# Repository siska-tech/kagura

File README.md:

# 

Kinetic Audio & Graphics Unified Rendering Architecture。
Tang Nano 9K（GW1NR-9）1枚で動く、外部ホスト制御のHDMIビデオ・サウンドチップです。ホストは32 byteのレジスタ窓だけを操作し、FPGAが背景・spriteの描画、音源の合成、HDMI（映像＋48kHz音声）出力を行います。

*720pデモのRTLシミュレーション出力（論理320×180を1280×720へ4倍表示）。実機モニターの撮影ではありません。[画像の生成元](docs/images/README.md)。*

デモ動画（YouTube）: [KAGURA-9: Custom HDMI Video & 6-Channel Sound Chip](https://www.youtube.com/shorts/ZjfHmth6I0A)

*実機構成: Raspberry Pi Pico（SPI/QSPIホスト）とTang Nano 9K。配線は[Pico firmware](https://github.com/siska-tech/kagura-sdk/blob/aae8699d8db01ed9825b37443b8ff8f3bb1cd14b/software/pico/README.md)を参照。*

## Picoキャリアボード

<table>
<tr>
<td></td>
<td></td>
</tr>
<tr><td>表面：Tang Nano 9K・XIAO RP2040</td><td>裏面：Raspberry Pi Pico</td></tr>
</table>

Raspberry Pi Pico・Tang Nano 9K・XIAO RP2040をまとめる、72×48mm・4層の試作キャリアボードです。USB-Cからの5V給電、USB-Aホスト端子、3.3V Grove I2C、GPIO拡張を備えます。表面にTang/XIAO、裏面にPicoを配置する構成です。

[ボード資料と製造データ](boards/pico-carrier-board/README_JP.md)に、KiCadプロジェクト、PCBに同期した回路図、JLCPCB向けガーバー・BOM・CPL、LCSC部品購入ガイドをまとめています。Basic RevAは設計レビュー・実機確認が残る試作版です。

*画像はTang Nano 9K・Pico・USB-Aコネクタのモデルを載せたKiCadの3Dレンダリングです。Tangは提供された3672版STEPを参考表示しています。一部部品モデルは省略しています。[モデルと積み高さの説明](boards/pico-carrier-board/kicad/models/README_JP.md)。実装済み基板の写真ではありません。*

## ショーケース

<table>
<tr>
<td></td>
<td></td>
<td></td>
</tr>
<tr>
<td></td>
<td></td>
<td></td>
</tr>
</table>

*すべて実機のHDMI出力のキャプチャです。説明付きの一覧は[ショーケース](https://github.com/siska-tech/kagura-sdk/blob/aae8699d8db01ed9825b37443b8ff8f3bb1cd14b/docs/showcase.md)にあります。*

## 仕様

| 分野 | 内容 |
|---|---|
| 画面 | 320×240（640×480p60へ2倍）または320×180（1280×720p60へ4倍）。bitstreamで選択 |
| 背景 | 1面、64×32 map、8×8 tile、1200 pattern（4bpp）、scroll、ライン別scroll表（8 entry） |
| sprite | 256個登録、16個/line、8×8・16×16、反転、behind |
| 色 | RGB444、16色×16 palette |
| 音源 | pulse 3、noise 1、wavetable 2。PSRAM版はPSRAM上のsigned 8bit PCM 2chを追加 |
| 音声 | 48kHz・16bitステレオ（HDMI） |
| メモリ | VRAM約49KiB（BSRAM）。PSRAM版は内蔵PSRAM 4MiBを公開し、PCM・COPYの元に使う |
| ホスト | SPI/QSPI（Raspberry Pi Pico等） |
| レジスタABI | 0.6（[レジスタ仕様](docs/register-map.md)） |

## 現在の状態

- **神楽デスクトップ**: [C言語で合成するGEM風デスクトップ](https://github.com/siska-tech/kagura-desktop)。別リポジトリ`kagura-desktop`で開発し、[kagura-sdk](https://github.com/siska-tech/kagura-sdk)の公開API（`kagura.tileplane`、`kagura.console`、`kagura_audio`等）だけを使う。MicroPythonから操作する。
  - 日本語のウィンドウ・メニュー・テキストフィールドを持つ。
  - 8 KBまでの日本語エディタ「神楽メモ帳」と、SKK日本語入力（候補ポップアップ、メニューバーの入力モード表示）を備える。
  - 分離前のファームウェア（このリポジトリから作成）で、全シーンの画面とVRAM読戻しのCRCがPCの結果と一致することを実機で検証済み。分離後のkagura-desktopのビルドは実機未検証。
- **音声とトラッカー（Phase 6）**: [ネイティブ音声HAL、KSNG曲フォーマット、決定的なプレイヤー](https://github.com/siska-tech/kagura-sdk/blob/aae8699d8db01ed9825b37443b8ff8f3bb1cd14b/software/audio/README.md)と、MicroPythonモジュール`kagura_audio`。
  - その上に、デスクトップ上で動く「神楽トラッカー」、波形エディタ、合成波形のスコープを実装。
  - 曲はCの配列として書き出し、単体のCゲームでも再生できる。
  - 実機のHDMI音声を録音して測定した: テンポのずれなし。通常のデスクトップ操作中の発音タイミングのずれは最大でおおむね5 ms、ウィンドウ移動中は8 ms。
  - 詳細は[実機受入](https://github.com/siska-tech/kagura-sdk/blob/aae8699d8db01ed9825b37443b8ff8f3bb1cd14b/software/audio/docs/hardware.md)。
- **KAGURA-UI（Phase 1）**: [MicroPython GUIの設計・API・デモ](https://github.com/siska-tech/kagura-sdk/blob/aae8699d8db01ed9825b37443b8ff8f3bb1cd14b/docs/kagura-ui.md)。既存Framebufferの排他所有、部分再描画、日本語、USB端末入力を実装。[RP2040のHDMI表示・操作・復帰・5376更新を検証](https://github.com/siska-tech/kagura-sdk/blob/aae8699d8db01ed9825b37443b8ff8f3bb1cd14b/docs/kagura-ui-validation.md)。
- **TileFramebuffer**: [320×240・16色の疑似フレームバッファ](https://github.com/siska-tech/kagura-sdk/blob/aae8699d8db01ed9825b37443b8ff8f3bb1cd14b/docs/framebuffer.md)をMicroPython SDKで提供。全1200セルを独立したpatternへ割り当て、ローカル描画とdirty転送を行う。[実機結果](https://github.com/siska-tech/kagura-sdk/blob/aae8699d8db01ed9825b37443b8ff8f3bb1cd14b/docs/framebuffer-results.md)は全量読戻し・PCM併用5分負荷・480pのユーザー目視に合格。[Viper描画高速化](https://github.com/siska-tech/kagura-sdk/blob/aae8699d8db01ed9825b37443b8ff8f3bb1cd14b/docs/framebuffer-viper-results.md)も両backendのCRC一致・各5分負荷で検証済み。[blit・ellipse・paint](https://github.com/siska-tech/kagura-sdk/blob/aae8699d8db01ed9825b37443b8ff8f3bb1cd14b/docs/framebuffer-primitives.md)もPC参照・実VRAM読戻しとの一致、PCM併用5分負荷、480pのユーザー目視で検証済み。
- **ABI 0.6（1,200タイル）の数値検証**: 公開タイル数を1,200枚へ拡張。ホスト4構成のP&R/STAとSRAM起動・境界検査、全1200枚の読戻し、PCM併用1時間連続動作、文字キャッシュ1072枠。詳細は[第3段階](docs/tile-1200-stage3.md)。[720pの目視・聴感](docs/tile-1200-visual.md)も確認済み。拡張の経緯は[1,200タイル対応の記録](docs/tile-1200-experiment.md)と[調査書](docs/tile-1200-feasibility.md)。
- **拡張前ABI 0.5の過去の実機記録**: 480p/720pの映像・音声（PCモニターとテレビの2機種）、内蔵sequencerのシューティングデモ、Raspberry Pi PicoからのSPI/QSPI制御（5MHz）、PSRAMへのupload・COPY・PCM 2chの連続再生。
- **未実施**: 複数sink×ケーブルでの反復・長時間の互換性試験、SPI/QSPIの10MHz動作。

詳細と既知の制約は[検証状況](docs/validation-status.md)を参照してください。

FPGA standaloneの`demo`／`demo720`はdeprecatedです。Picoホスト上のデモ・診断を利用してください。旧ソースと過去の検証記録は残しますが、1,200タイル対応の受入対象から外します。

## はじめかた

1. [アーキテクチャ](docs/architecture.md)で全体とビルド構成を確認する。
2. [ビルド・テスト](docs/build-and-test.md)の手順でbitstreamを作り、SRAMへ書き込む。主な動作確認はPicoホストの`qspipsram`／`qspipsram720`構成で行う。
3. Picoから操作する場合は`qspipsram`（または`spi`/`qspi`）を書き込み、[Pico firmware](https://github.com/siska-tech/kagura-sdk/blob/aae8699d8db01ed9825b37443b8ff8f3bb1cd14b/software/pico/README.md)の`diag`・`show`・`stress`を実行する。
4. 自分のホストから使う場合は[プログラミングガイド](https://github.com/siska-tech/kagura-sdk/blob/aae8699d8db01ed9825b37443b8ff8f3bb1cd14b/docs/programming-guide.md)と[レジスタ仕様](docs/register-map.md)を読む。

```sh
bash tools/test-verilator.sh                 # RTL回帰（WSL/Linux）
```

```powershell
powershell -NoProfile -ExecutionPolicy Bypass -File tools/check-design.ps1
powershell -NoProfile -ExecutionPolicy Bypass -File tools/gen-registers.ps1 -Check
```

文書の一覧は[ドキュメント案内](docs/README.md)にあります。

[MicroPythonドライバ](https://github.com/siska-tech/kagura-sdk/blob/aae8699d8db01ed9825b37443b8ff8f3bb1cd14b/software/micropython/README.md)は、SPI/QSPI制御とUARTキーボード入力・HDMI REPL、REPL出力とアプリ画面の8×8日本語表示（美咲ゴシック）を提供します。導入方法と実機検証の残作業はリンク先を参照してください。

[実機紹介プレゼンテーション](https://github.com/siska-tech/kagura-sdk/blob/aae8699d8db01ed9825b37443b8ff8f3bb1cd14b/software/micropython/examples/showcase.md)は、日本語の疑似256色スライドからトンネル・ネオン風の描画、[PROJECT STARFALLのMicroPython移植](https://github.com/siska-tech/kagura-sdk/blob/aae8699d8db01ed9825b37443b8ff8f3bb1cd14b/software/micropython/examples/starfall.md)、桜吹雪までを自動進行します。480p FULL+PSRAM構成を使用します。

ただし現行のファームウェアでは、描画の章のあと、STARFALLの章を読み込むところでメモリ不足で止まります。桜吹雪も単体で開始時に止まります。STARFALLは単体なら動きます。原因は調査中です（[ショーケースの注記](https://github.com/siska-tech/kagura-sdk/blob/aae8699d8db01ed9825b37443b8ff8f3bb1cd14b/docs/showcase.md#撮影時の注記)）。

## リポジトリ

KAGURA-9は3つのリポジトリに分かれています。依存は一方向です（kagura-desktop → kagura-sdk → kagura）。

| リポジトリ | 内容 |
|---|---|
| **siska-tech/kagura**（ここ） | RTL、シミュレーション、ボード、レジスタ定義`spec/registers.json`と生成器、bitstreamとリリース、ハードウェア仕様 |
| [siska-tech/kagura-sdk](https://github.com/siska-tech/kagura-sdk) | ホストのドライバと公開API（C、MicroPython）、MicroPythonボードとファームウェア統合、UI・日本語・音声ライブラリ、例、SDKの文書。生成したレジスタ定数を写して持ち、元にしたkaguraのcommitを`hardware.lock`で固定する |
| [siska-tech/kagura-desktop](https://github.com/siska-tech/kagura-desktop) | 神楽デスクトップとアプリ。kagura-sdkの公開APIだけを使い、SDKのcommitを`sdk/kagura.ref`で固定する |

[6502対応は別リポジトリに切り出しました](https://github.com/siska-tech/kagura-6502)。

kaguraからkagura-sdkへのビルド依存はありません。CIだけが`sdk.lock`のkagura-sdkを取得し、そのレジスタ定数が`spec/registers.json`から生成したものと一致するかを`tools/check-sdk.sh`で検査します。仕様を変えた場合はkaguraが先に進み、SDKが`tools/gen-registers.ps1 -SdkDir`で再生成して追従します。

| path | 内容 |
|---|---|
| `rtl/` | RTL（core、vdp、audio、memory、hdmi、bus、platform）。[RTL一覧](rtl/README.md) |
| `boards/pico-carrier-board/` | PicoキャリアボードのKiCad・同期回路図・製造データ・部品購入ガイド。[ボード資料](boards/pico-carrier-board/README_JP.md) |
| `boards/tang-nano-9k/` | board top、CST/SDC、ピン一覧。[ボード資料](boards/tang-nano-9k/README.md) |
| `sim/` | SystemVerilog testbenchと参照モデル。[試験一覧](sim/README.md) |
| `spec/` | 機械可読のレジスタ定義と設計予算 |
| `tools/` | 合成・生成・検査・書込みのscript |
| `docs/` | 仕様と検証の文書。[SDK分離の記録](docs/sdk-extraction.md) |
| `third_party/` | 固定revisionのhdl-util/hdmi |

## ライセンス

オリジナル成果物はApache-2.0。第三者のRTL・フォント等は`third_party/`と各ファイルの記載に従います。[第三者IP方針](THIRD_PARTY.md)を参照してください。

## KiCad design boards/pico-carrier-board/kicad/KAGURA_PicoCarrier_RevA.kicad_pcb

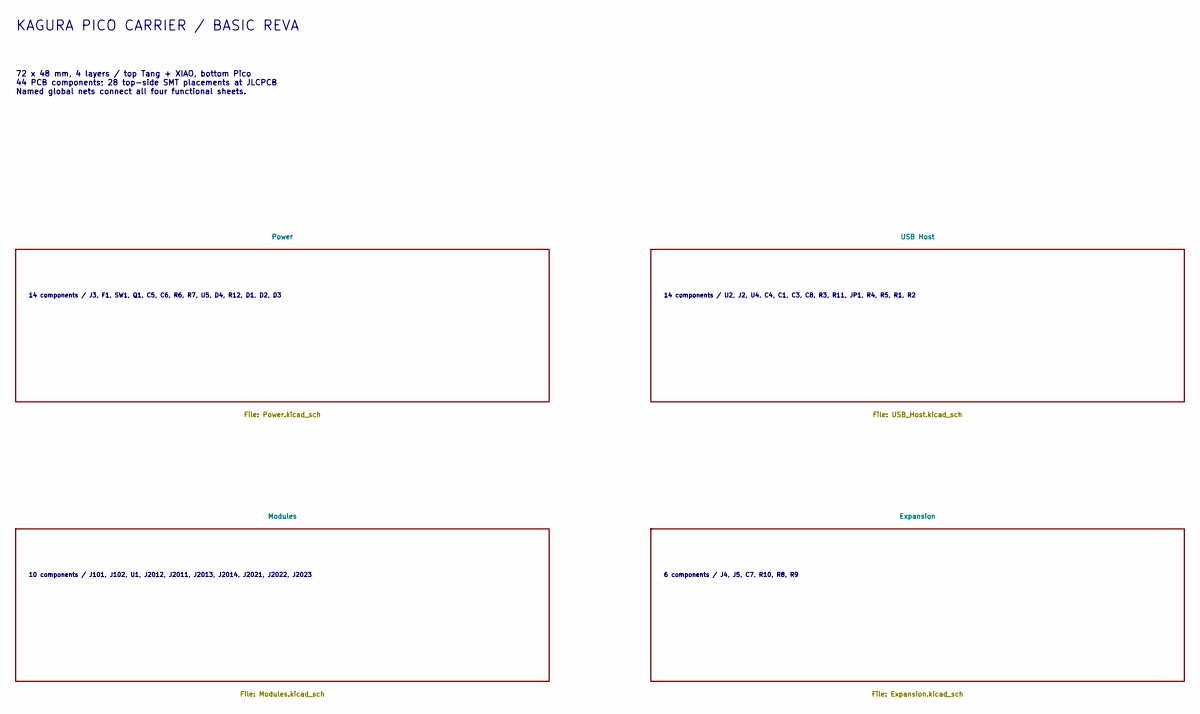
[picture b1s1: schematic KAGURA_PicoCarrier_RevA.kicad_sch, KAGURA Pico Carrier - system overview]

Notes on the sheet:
KAGURA PICO CARRIER / BASIC REVA
72 x 48 mm, 4 layers / top Tang + XIAO, bottom Pico 44 PCB components; 28 top-side SMT placements at JLCPCB Named global nets connect all four functional sheets.
14 components / J3, F1, SW1, Q1, C5, C6, R6, R7, U5, D4, R12, D1, D2, D3
14 components / U2, J2, U4, C4, C1, C3, C8, R3, R11, JP1, R4, R5, R1, R2
10 components / J101, J102, U1, J2012, J2011, J2013, J2014, J2021, J2022, J2023
6 components / J4, J5, C7, R10, R8, R9

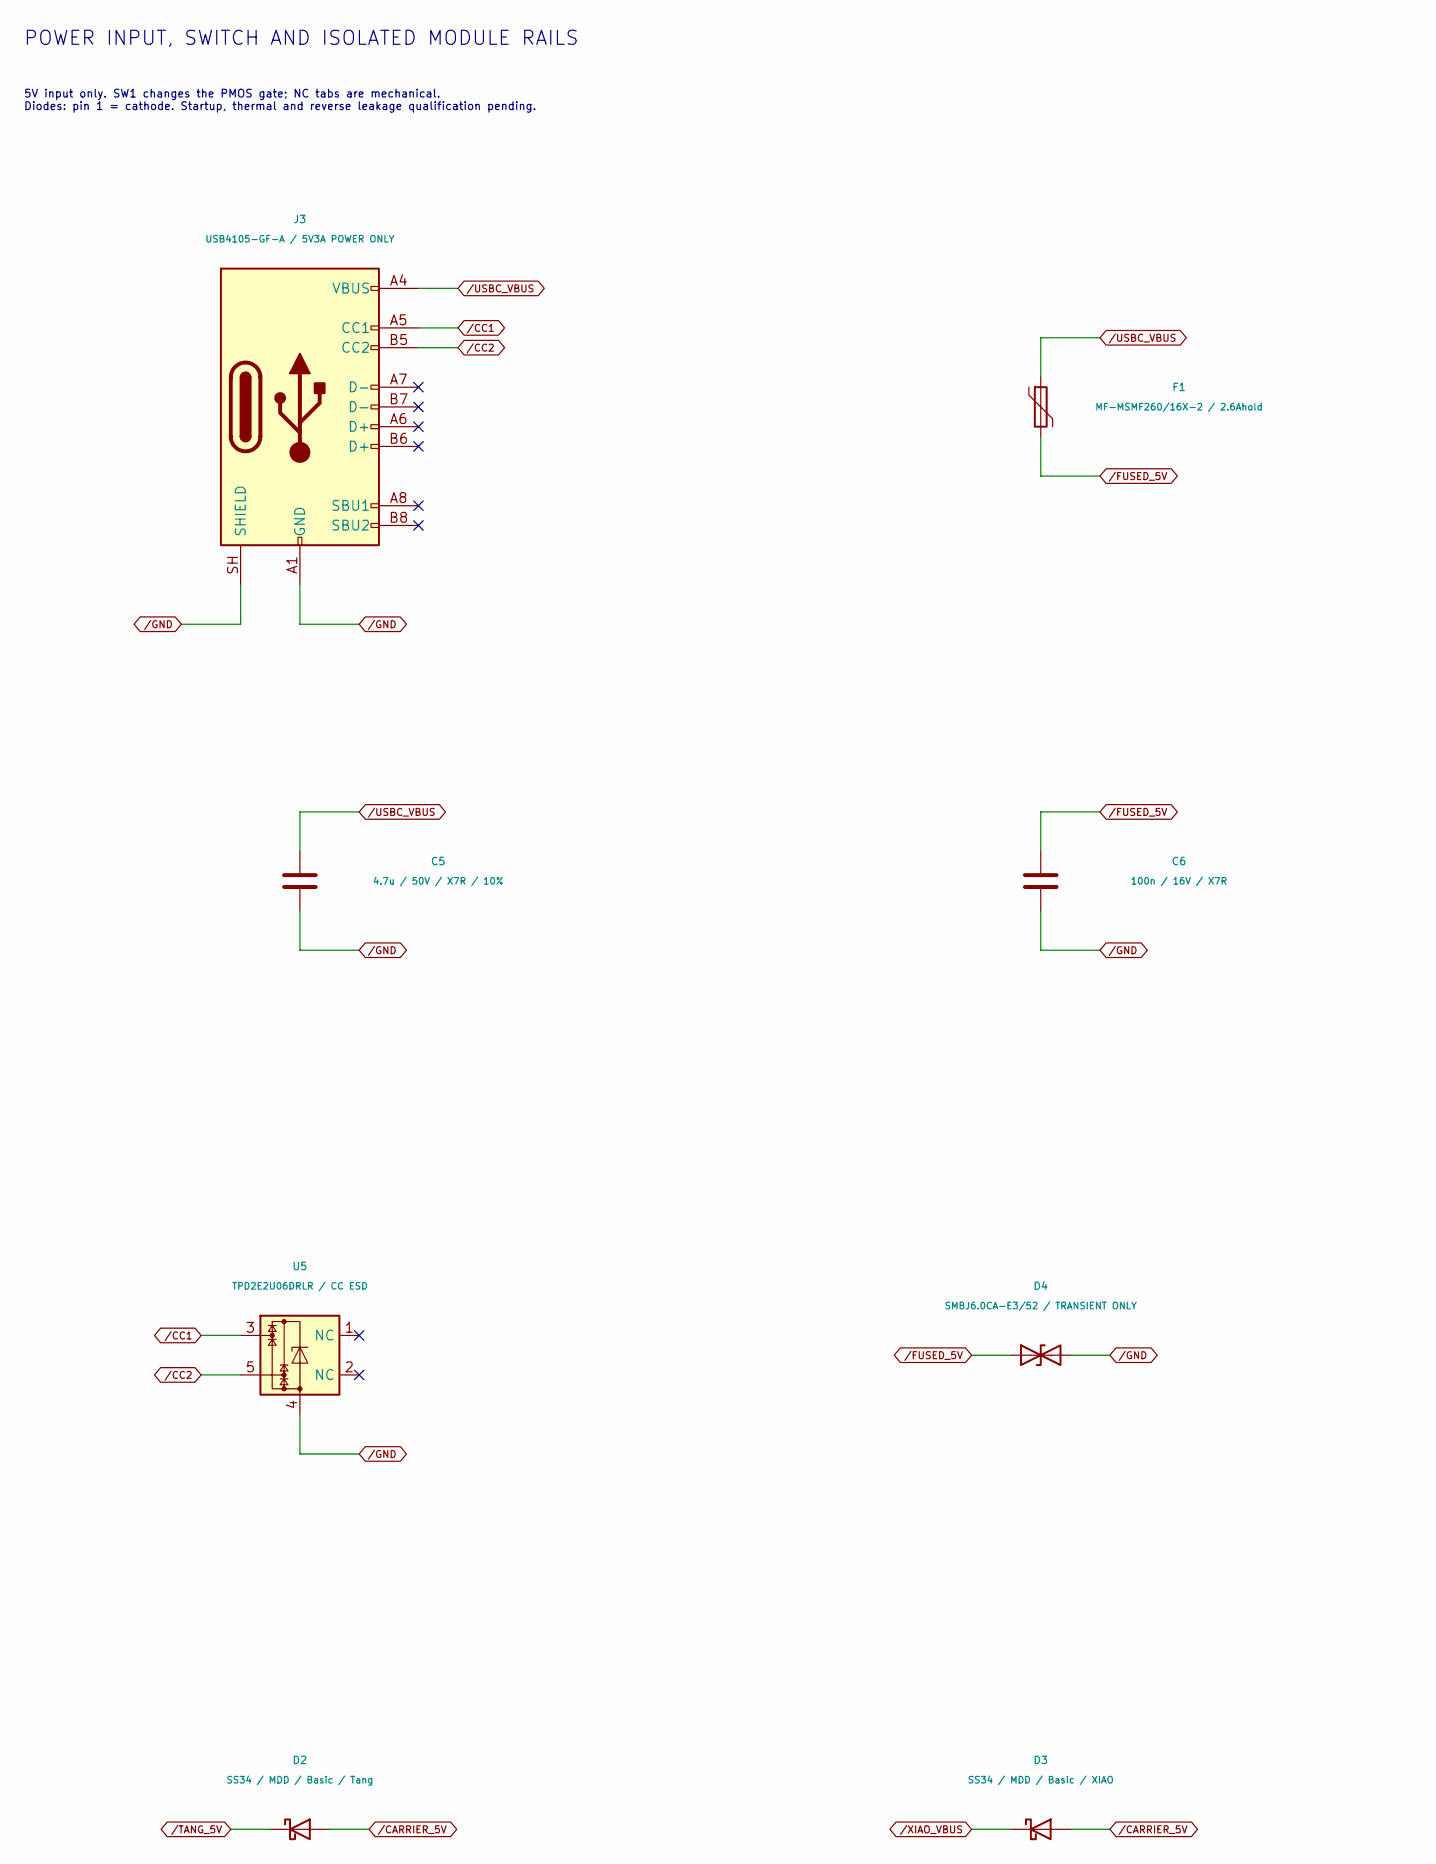
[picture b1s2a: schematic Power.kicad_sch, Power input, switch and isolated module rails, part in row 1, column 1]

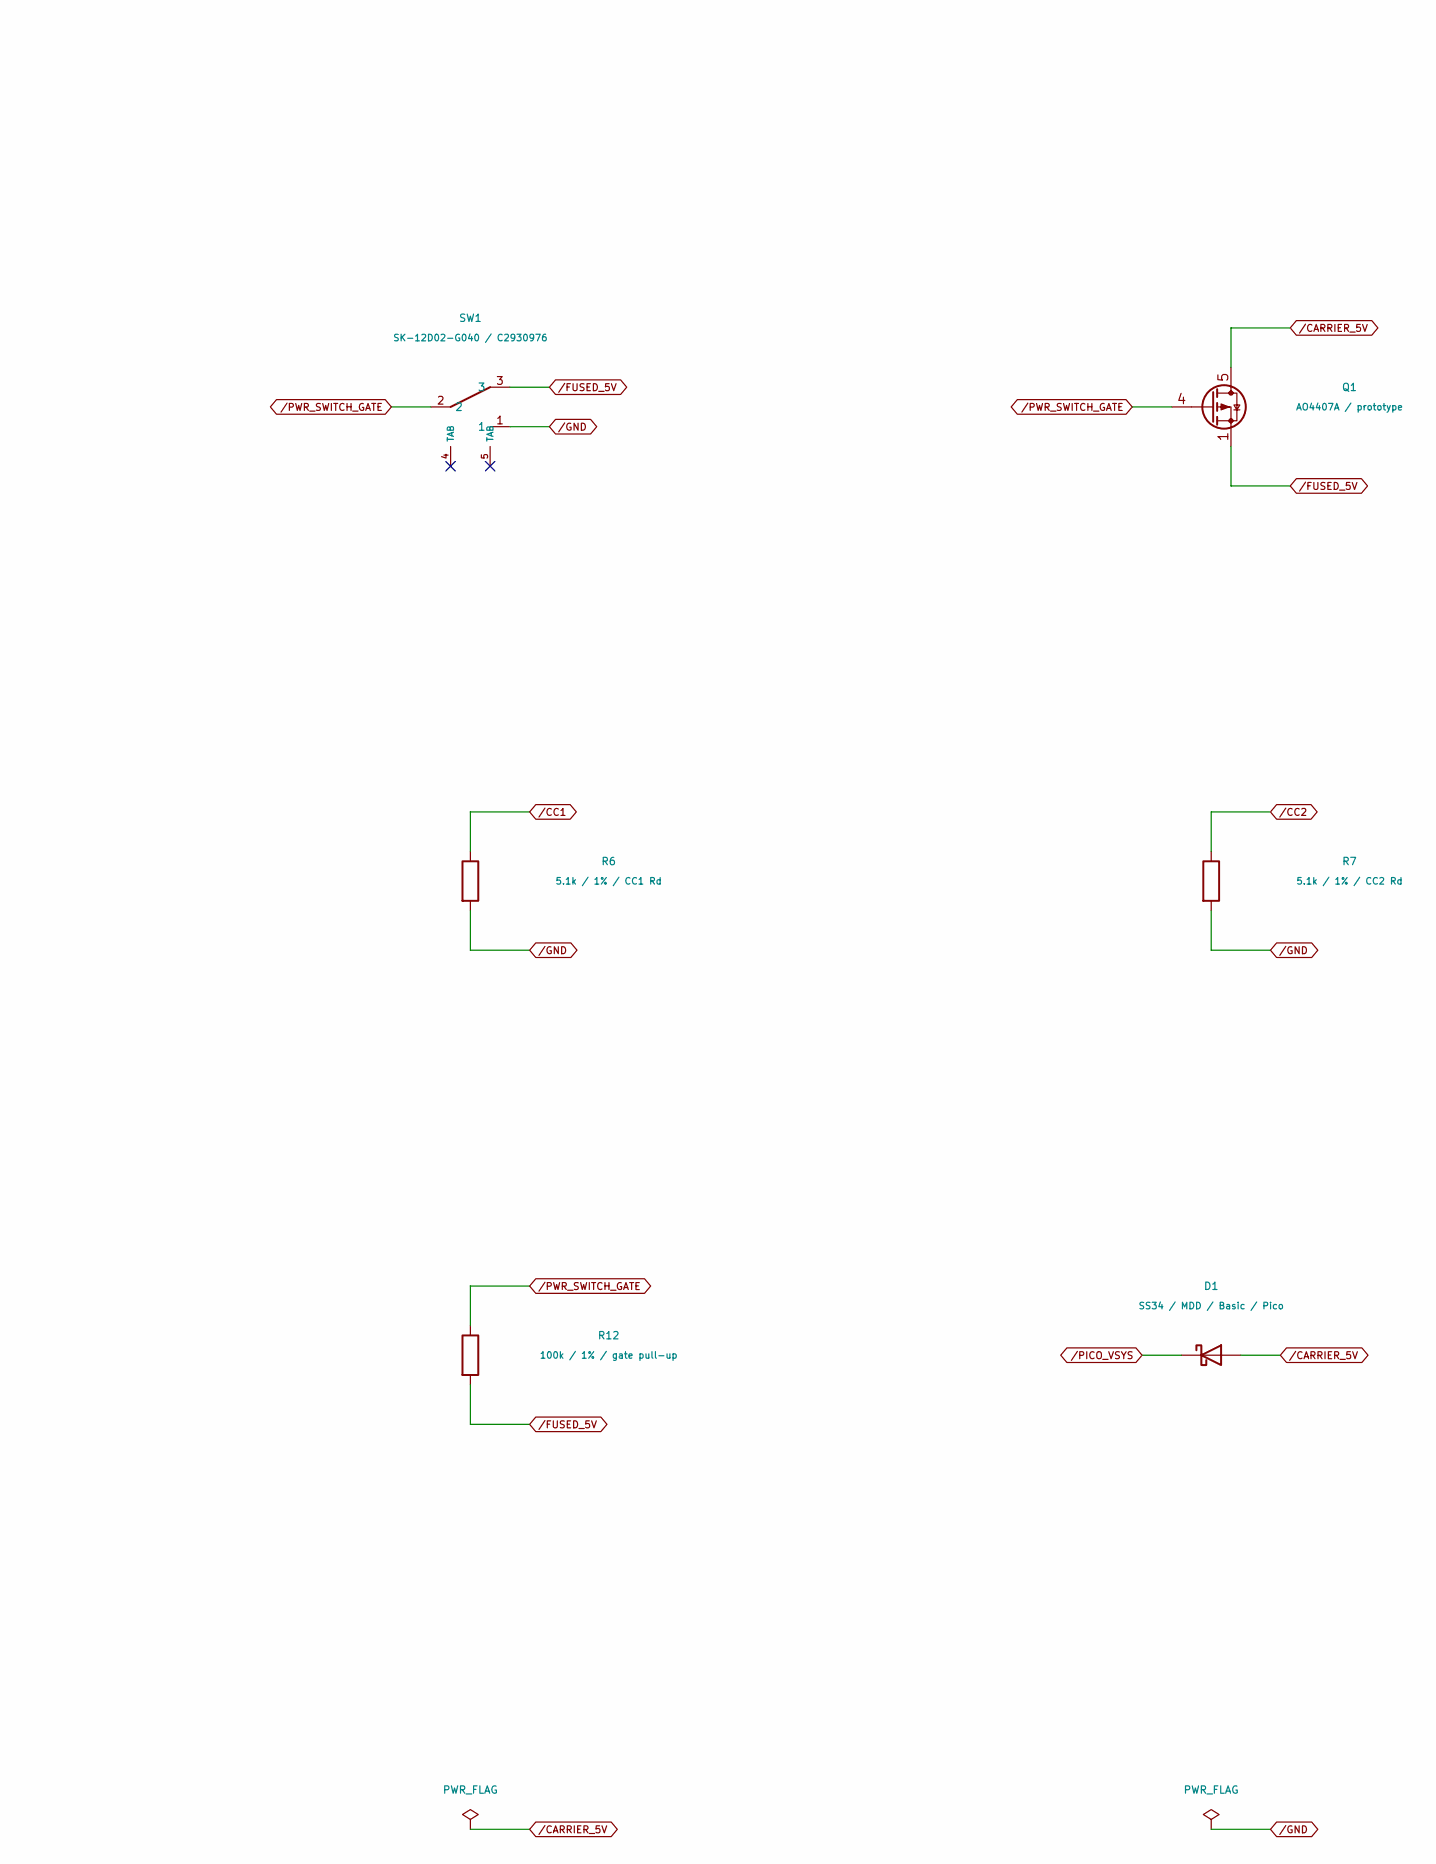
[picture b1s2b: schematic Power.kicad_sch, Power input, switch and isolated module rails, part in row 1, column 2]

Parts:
C5: 4.7u / 50V / X7R / 10%; C_1206_3216Metric
C6: 100n / 16V / X7R; C6
D1: SS34 / MDD / Basic / Pico; D_SMA
D2: SS34 / MDD / Basic / Tang; D_SMA
D3: SS34 / MDD / Basic / XIAO; D_SMA
D4: SMBJ6.0CA-E3/52 / TRANSIENT ONLY; D4
F1: MF-MSMF260/16X-2 / 2.6Ahold; F1
J3: USB4105-GF-A / 5V3A POWER ONLY; J3
Q1: AO4407A / prototype; SOIC-8_3.9x4.9mm_P1.27mm
R6: 5.1k / 1% / CC1 Rd; R6
R7: 5.1k / 1% / CC2 Rd; R7
R12: 100k / 1% / gate pull-up; R_0603_1608Metric
SW1: SK-12D02-G040 / C2930976; SW1
U5: TPD2E2U06DRLR / CC ESD; U5

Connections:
/CARRIER_5V: D1.2 (A), D2.2 (A), D3.2 (A), Q1.5 (D), Q1.6 (D), Q1.7 (D), Q1.8 (D); also elsewhere on the board
/CC1: J3.A5 (CC1), R6.1, U5.3
/CC2: J3.B5 (CC2), R7.1, U5.5
/FUSED_5V: C6.1, D4.1 (A1), F1.2, Q1.1 (S), Q1.2 (S), Q1.3 (S), R12.2, SW1.3
/GND: C5.2, C6.2, D4.2 (A2), J3.A1 (GND), J3.A12 (GND), J3.B1 (GND), J3.B12 (GND), J3.SH (SHIELD), R6.2, R7.2, SW1.1, U5.4; also elsewhere on the board
/PICO_VSYS: D1.1 (K); also elsewhere on the board
/PWR_SWITCH_GATE: Q1.4 (G), R12.1, SW1.2
/TANG_5V: D2.1 (K); also elsewhere on the board
/USBC_VBUS: C5.1, F1.1, J3.A4 (VBUS), J3.A9 (VBUS), J3.B4 (VBUS), J3.B9 (VBUS)
/XIAO_VBUS: D3.1 (K); also elsewhere on the board

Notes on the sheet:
POWER INPUT, SWITCH AND ISOLATED MODULE RAILS
5V input only. SW1 changes the PMOS gate; NC tabs are mechanical. Diodes: pin 1 = cathode. Startup, thermal and reverse leakage qualification pending.

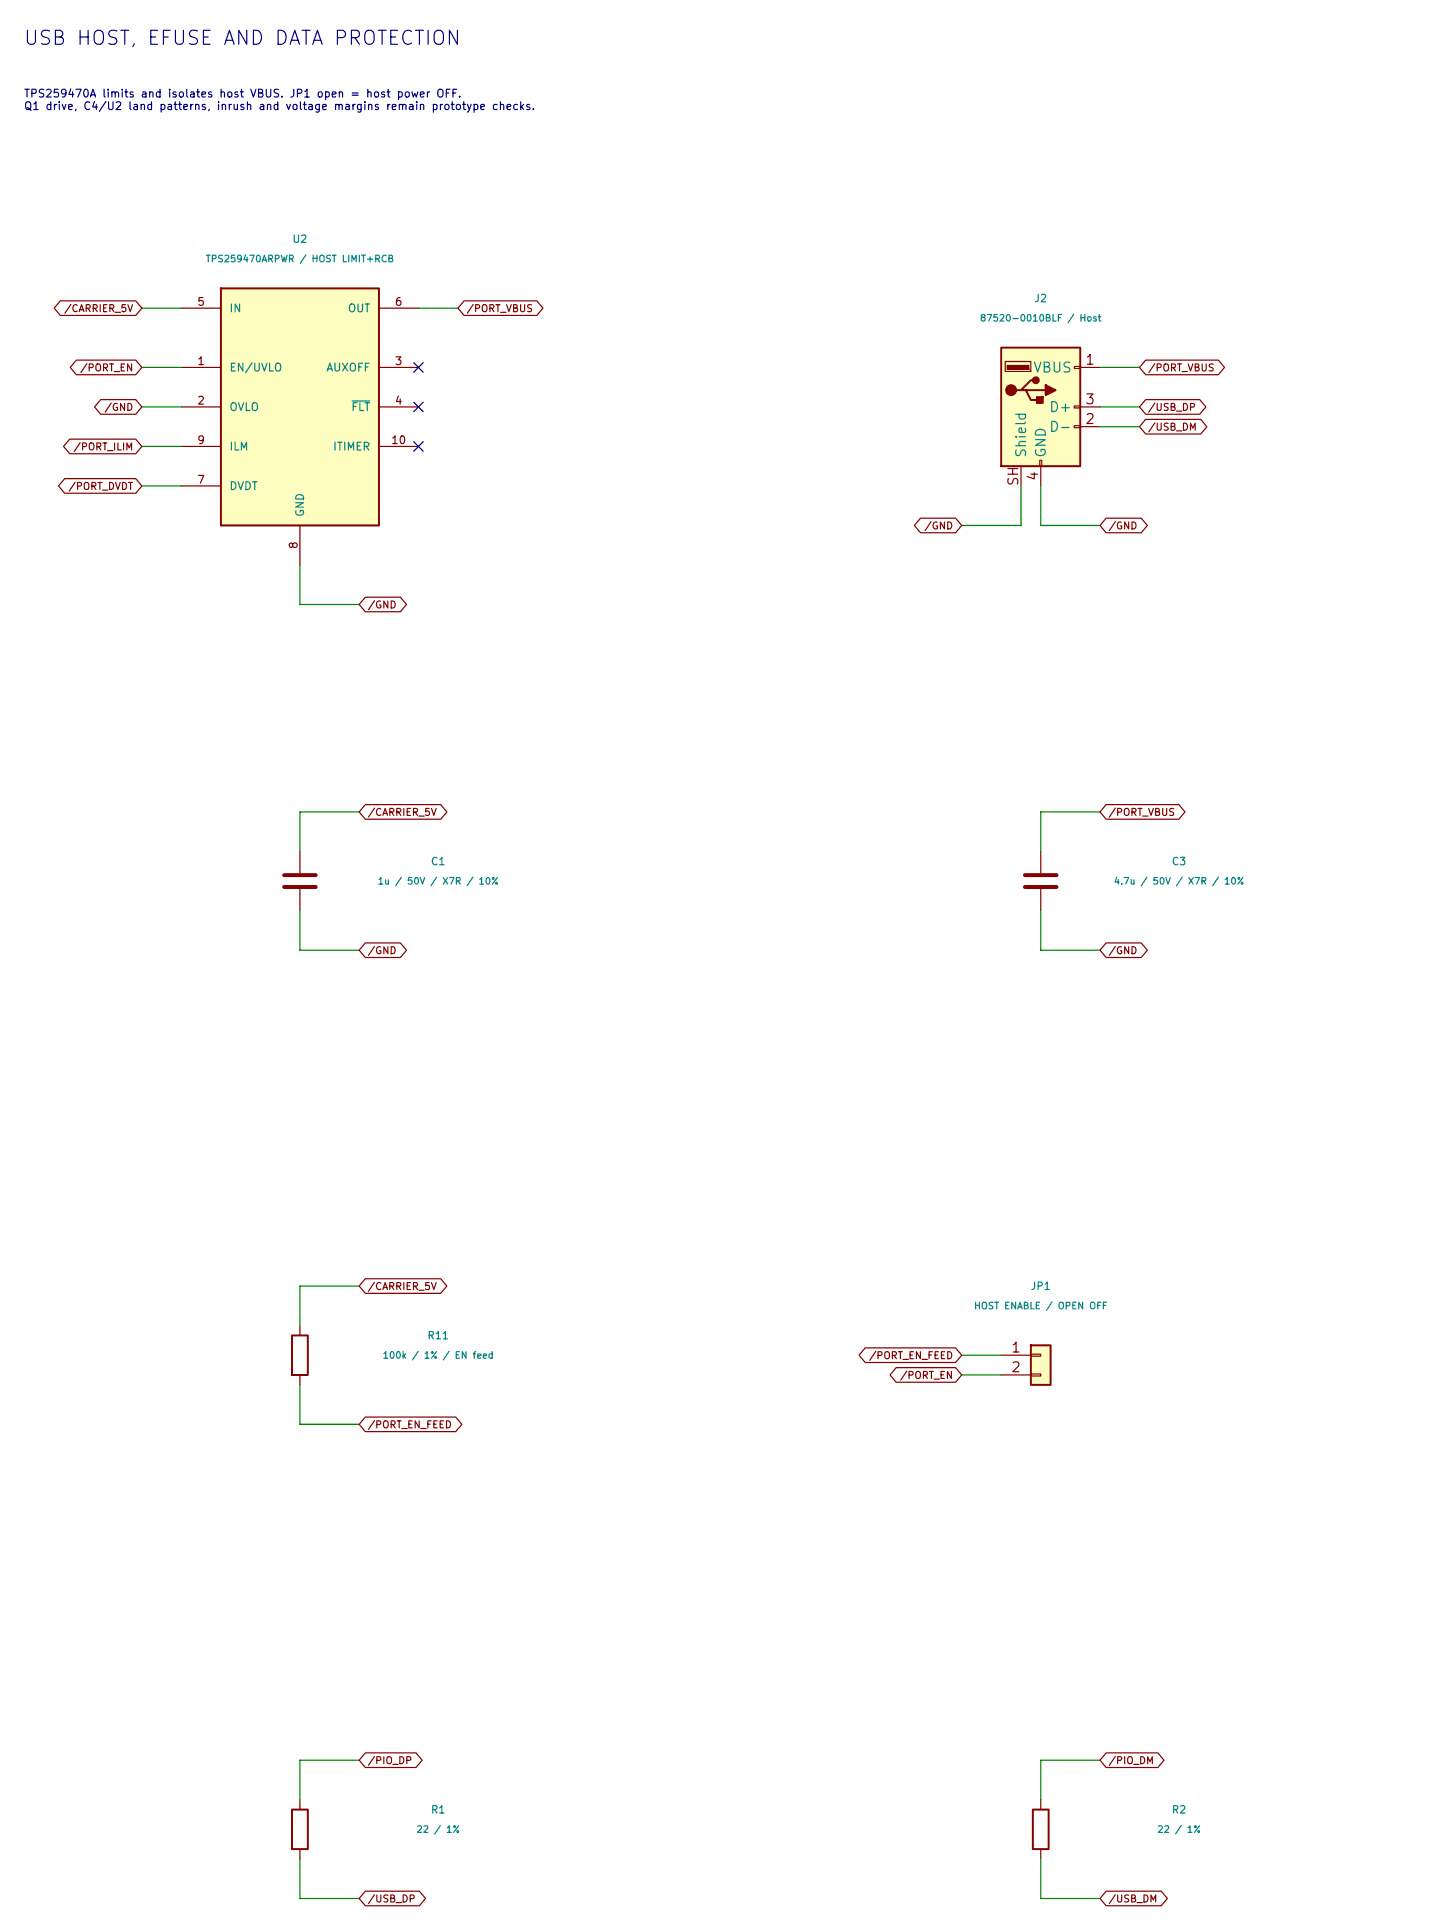
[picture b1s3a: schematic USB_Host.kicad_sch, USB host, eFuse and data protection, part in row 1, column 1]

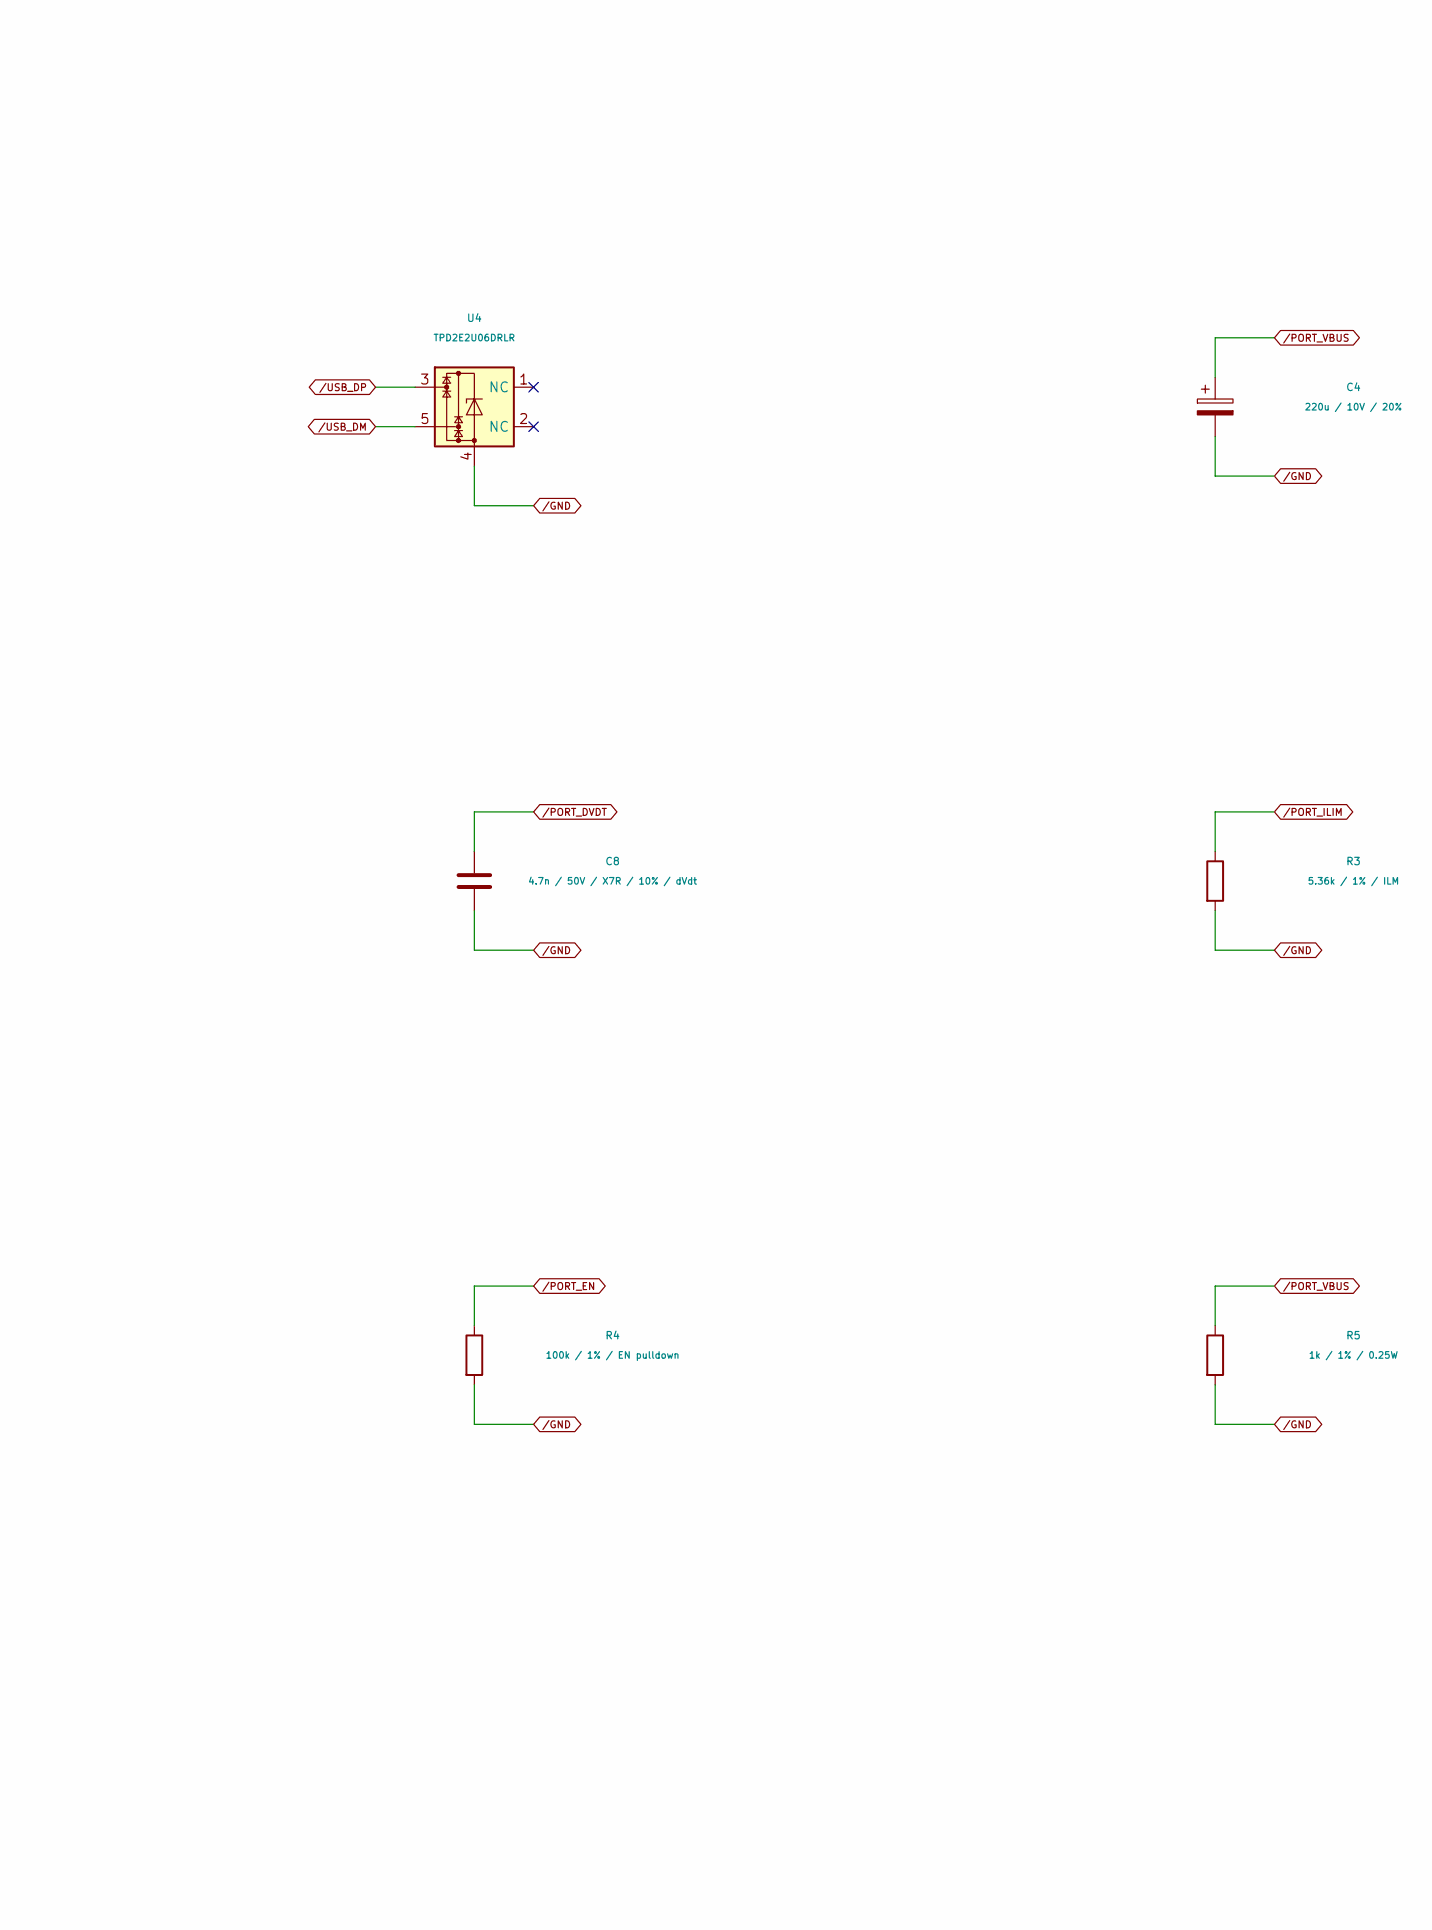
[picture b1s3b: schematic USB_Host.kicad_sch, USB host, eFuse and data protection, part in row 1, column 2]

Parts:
C1: 1u / 50V / X7R / 10%; C1
C3: 4.7u / 50V / X7R / 10%; C_1206_3216Metric
C4: 220u / 10V / 20%; C4
C8: 4.7n / 50V / X7R / 10% / dVdt; C8
J2: 87520-0010BLF / Host; J2
JP1: HOST ENABLE / OPEN OFF; JP1
R1: 22 / 1%; R1
R2: 22 / 1%; R2
R3: 5.36k / 1% / ILM; R3
R4: 100k / 1% / EN pulldown; R4
R5: 1k / 1% / 0.25W; R5
R11: 100k / 1% / EN feed; R11
U2: TPS259470ARPWR / HOST LIMIT+RCB; U2
U4: TPD2E2U06DRLR; U4

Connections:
/CARRIER_5V: C1.1, R11.1, U2.5 (IN); also elsewhere on the board
/GND: C1.2, C3.2, C4.2, C8.2, J2.4 (GND), J2.SH (Shield), R3.2, R4.2, R5.2, U2.2 (OVLO), U2.8 (GND), U4.4; also elsewhere on the board
/PIO_DM: R2.1; also elsewhere on the board
/PIO_DP: R1.1; also elsewhere on the board
/PORT_DVDT: C8.1, U2.7 (DVDT)
/PORT_EN: JP1.2, R4.1, U2.1 (EN/UVLO)
/PORT_EN_FEED: JP1.1, R11.2
/PORT_ILIM: R3.1, U2.9 (ILM)
/PORT_VBUS: C3.1, C4.1, J2.1 (VBUS), R5.1, U2.6 (OUT)
/USB_DM: J2.2 (D-), R2.2, U4.5
/USB_DP: J2.3 (D+), R1.2, U4.3

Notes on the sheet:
USB HOST, EFUSE AND DATA PROTECTION
TPS259470A limits and isolates host VBUS. JP1 open = host power OFF. Q1 drive, C4/U2 land patterns, inrush and voltage margins remain prototype checks.

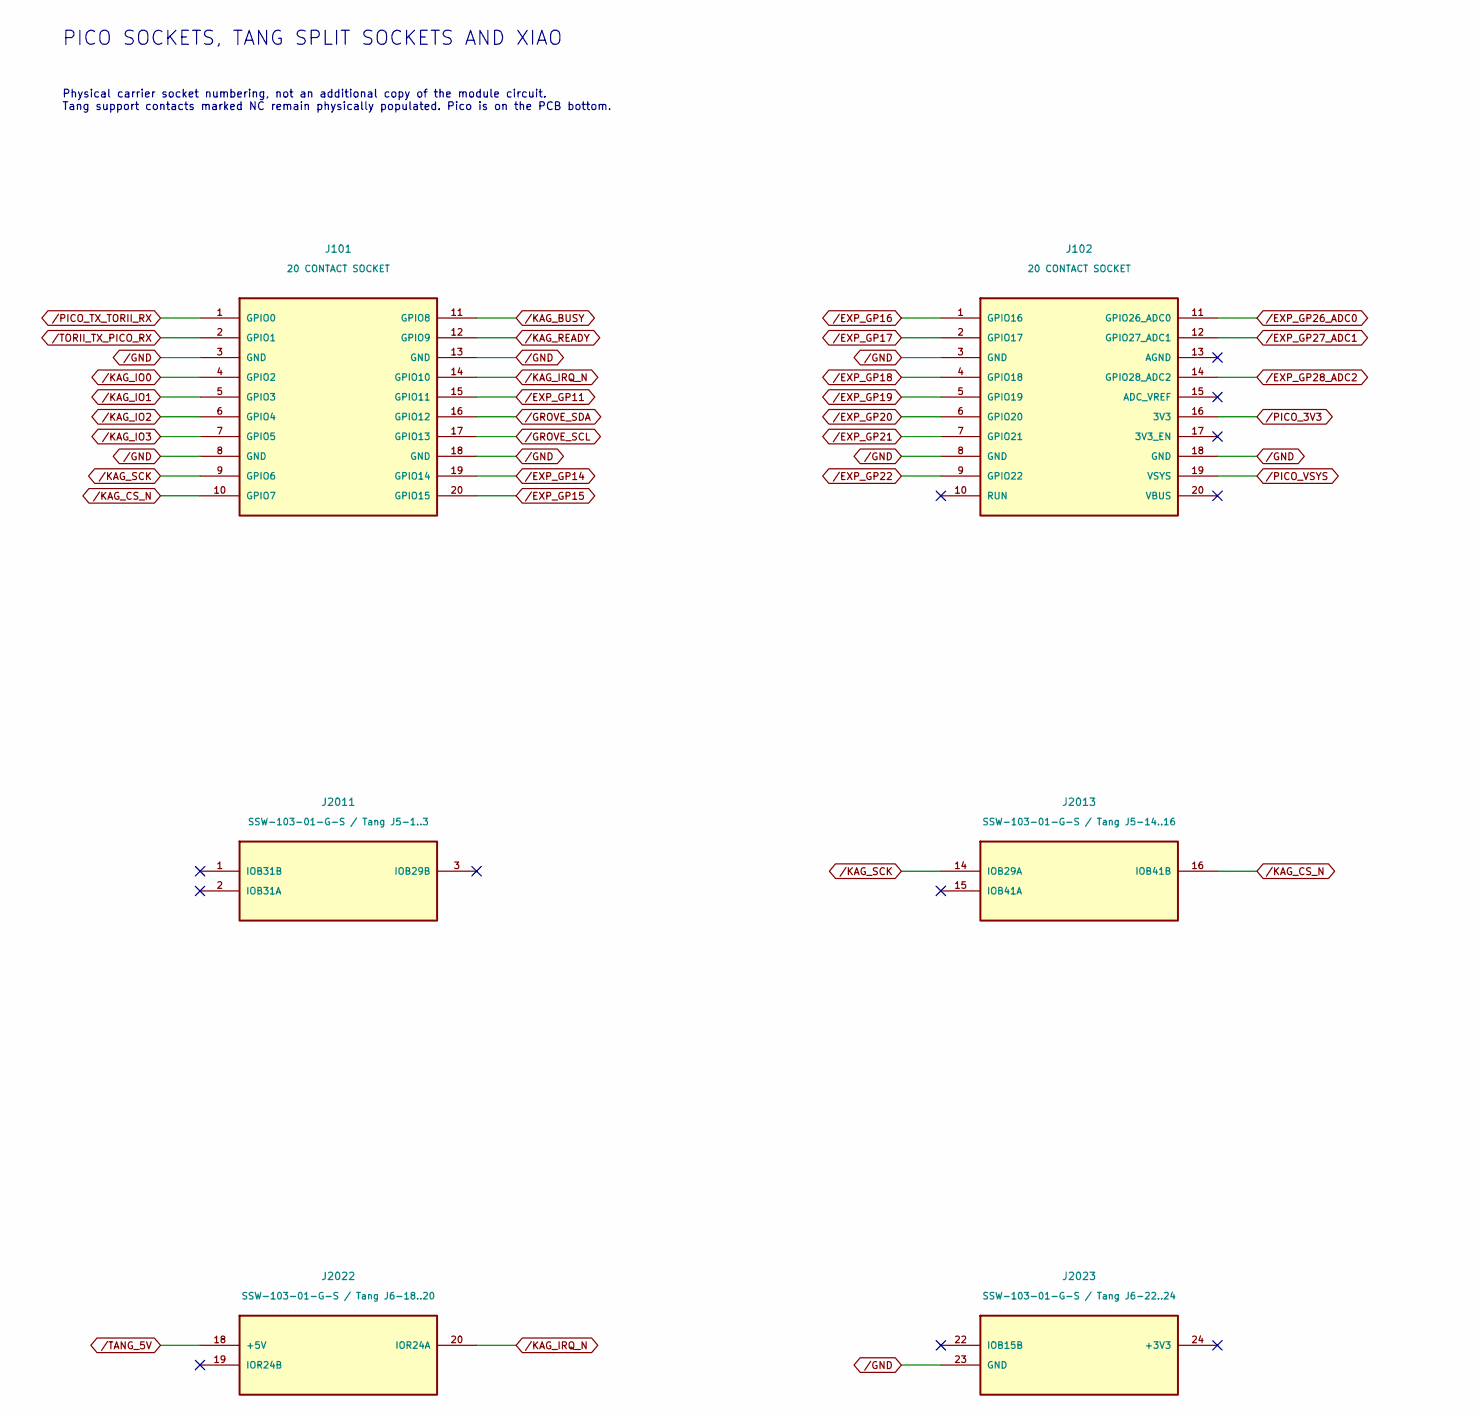
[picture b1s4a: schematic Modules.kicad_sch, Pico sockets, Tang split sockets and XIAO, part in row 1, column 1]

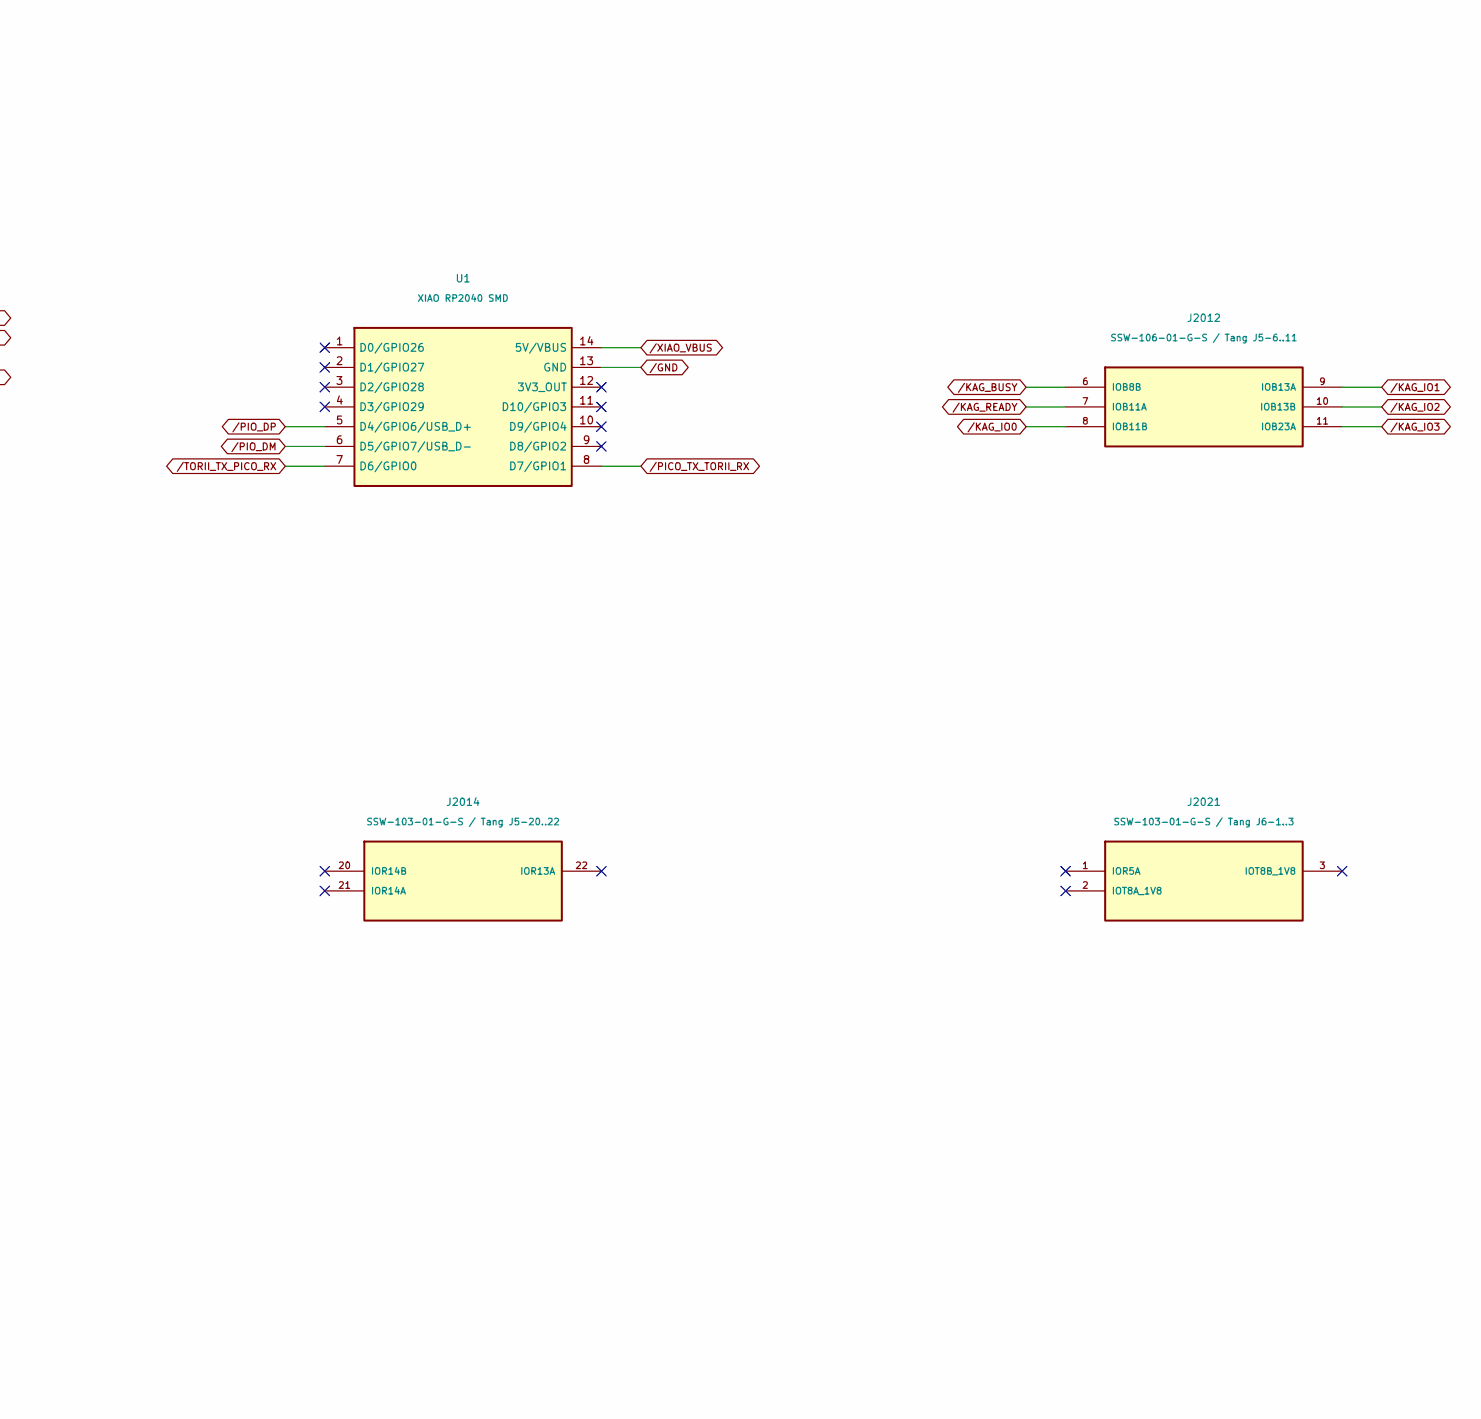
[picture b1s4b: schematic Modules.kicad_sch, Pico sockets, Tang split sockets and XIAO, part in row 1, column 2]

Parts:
J101: 20 CONTACT SOCKET; J101
J102: 20 CONTACT SOCKET; J102
J2011: SSW-103-01-G-S / Tang J5-1..3; J201A
J2012: SSW-106-01-G-S / Tang J5-6..11; J201B
J2013: SSW-103-01-G-S / Tang J5-14..16; J201C
J2014: SSW-103-01-G-S / Tang J5-20..22; J201D
J2021: SSW-103-01-G-S / Tang J6-1..3; J202A
J2022: SSW-103-01-G-S / Tang J6-18..20; J202B
J2023: SSW-103-01-G-S / Tang J6-22..24; J202C
U1: XIAO RP2040 SMD; U1

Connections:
/EXP_GP11: J101.15 (A1.15); also elsewhere on the board
/EXP_GP14: J101.19 (A1.19); also elsewhere on the board
/EXP_GP15: J101.20 (A1.20); also elsewhere on the board
/EXP_GP16: J102.1 (A1.21); also elsewhere on the board
/EXP_GP17: J102.2 (A1.22); also elsewhere on the board
/EXP_GP18: J102.4 (A1.24); also elsewhere on the board
/EXP_GP19: J102.5 (A1.25); also elsewhere on the board
/EXP_GP20: J102.6 (A1.26); also elsewhere on the board
/EXP_GP21: J102.7 (A1.27); also elsewhere on the board
/EXP_GP22: J102.9 (A1.29); also elsewhere on the board
/EXP_GP26_ADC0: J102.11 (A1.31); also elsewhere on the board
/EXP_GP27_ADC1: J102.12 (A1.32); also elsewhere on the board
/EXP_GP28_ADC2: J102.14 (A1.34); also elsewhere on the board
/GND: J101.3 (A1.3), J101.8 (A1.8), J101.13 (A1.13), J101.18 (A1.18), J102.3 (A1.23), J102.8 (A1.28), J102.18 (A1.38), J2023.23 (A2.J6-23), U1.13 (U1.13); also elsewhere on the board
/GROVE_SCL: J101.17 (A1.17); also elsewhere on the board
/GROVE_SDA: J101.16 (A1.16); also elsewhere on the board
/KAG_BUSY: J101.11 (A1.11), J2012.6 (A2.J5-6)
/KAG_CS_N: J101.10 (A1.10), J2013.16 (A2.J5-16)
/KAG_IO0: J101.4 (A1.4), J2012.8 (A2.J5-8)
/KAG_IO1: J101.5 (A1.5), J2012.9 (A2.J5-9)
/KAG_IO2: J101.6 (A1.6), J2012.10 (A2.J5-10)
/KAG_IO3: J101.7 (A1.7), J2012.11 (A2.J5-11)
/KAG_IRQ_N: J101.14 (A1.14), J2022.20 (A2.J6-20); also elsewhere on the board
/KAG_READY: J101.12 (A1.12), J2012.7 (A2.J5-7)
/KAG_SCK: J101.9 (A1.9), J2013.14 (A2.J5-14)
/PICO_3V3: J102.16 (A1.36); also elsewhere on the board
/PICO_TX_TORII_RX: J101.1 (A1.1), U1.8 (U1.8)
/PICO_VSYS: J102.19 (A1.39); also elsewhere on the board
/PIO_DM: U1.6 (U1.6); also elsewhere on the board
/PIO_DP: U1.5 (U1.5); also elsewhere on the board
/TANG_5V: J2022.18 (A2.J6-18); also elsewhere on the board
/TORII_TX_PICO_RX: J101.2 (A1.2), U1.7 (U1.7)
/XIAO_VBUS: U1.14 (U1.14); also elsewhere on the board

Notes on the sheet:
PICO SOCKETS, TANG SPLIT SOCKETS AND XIAO
Physical carrier socket numbering, not an additional copy of the module circuit. Tang support contacts marked NC remain physically populated. Pico is on the PCB bottom.
